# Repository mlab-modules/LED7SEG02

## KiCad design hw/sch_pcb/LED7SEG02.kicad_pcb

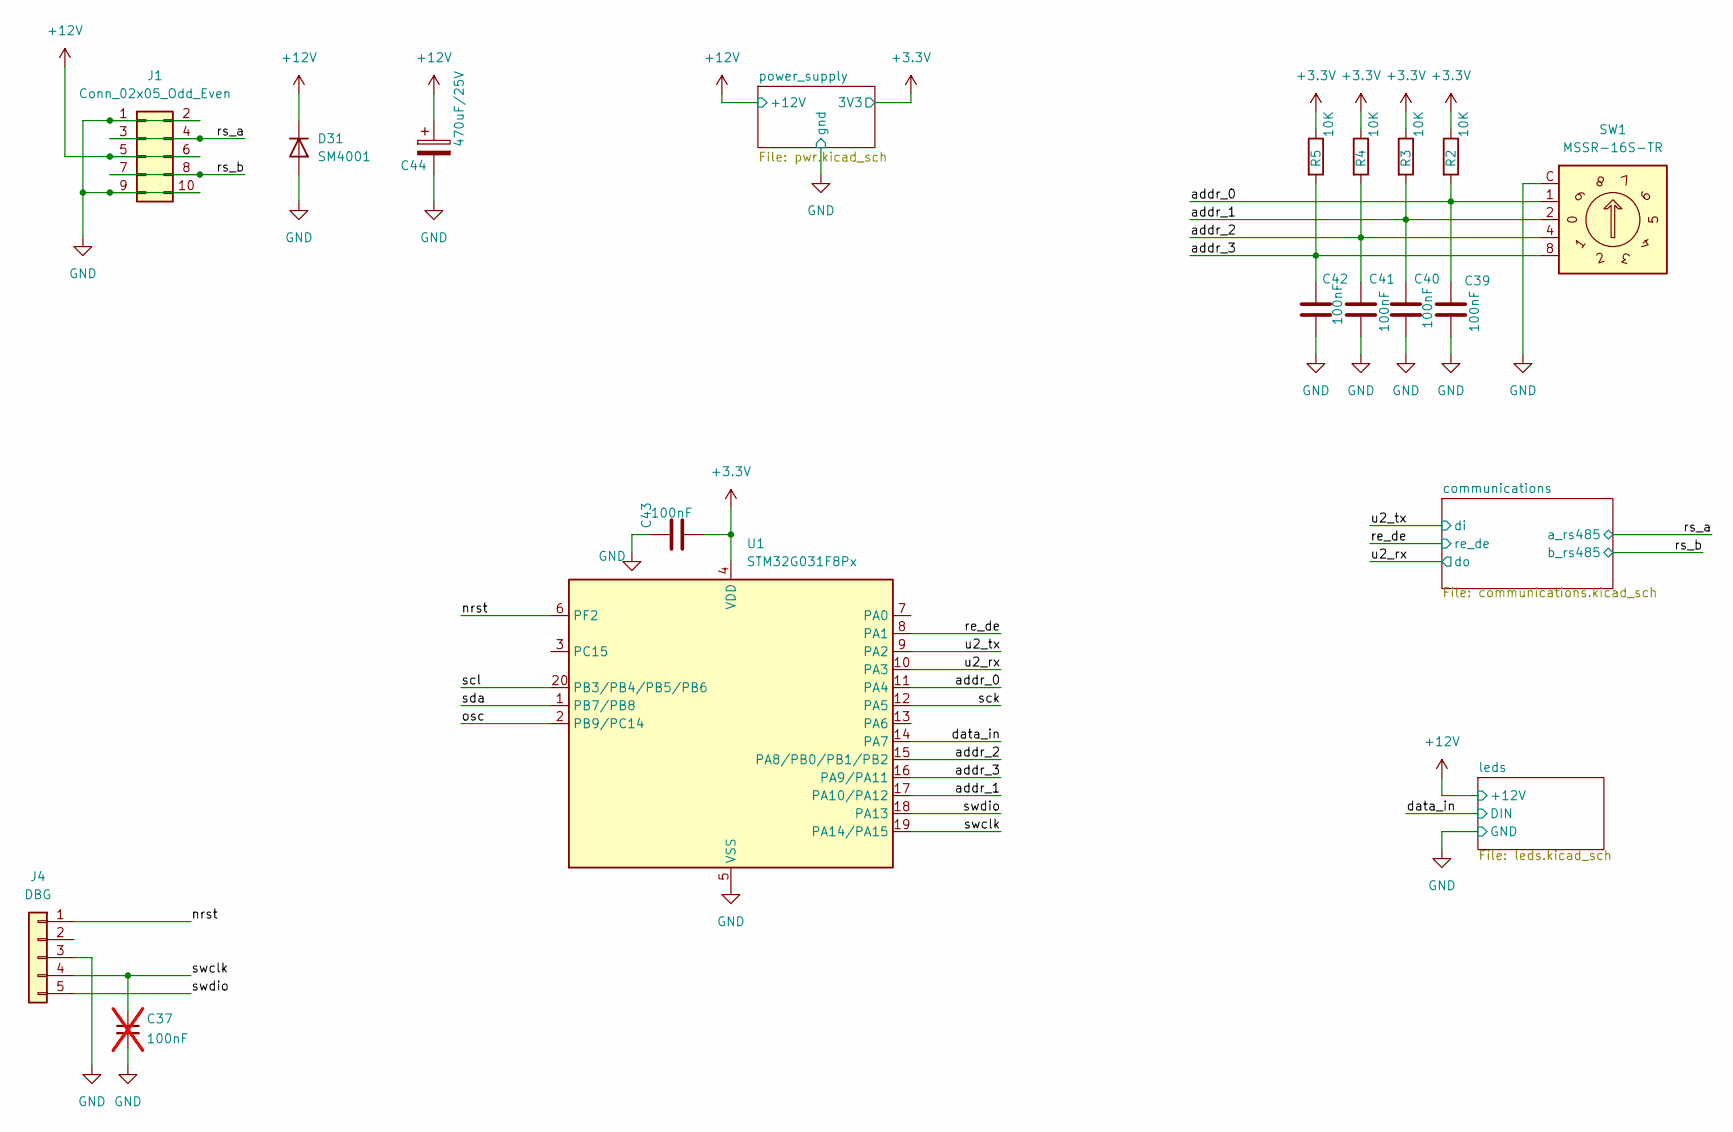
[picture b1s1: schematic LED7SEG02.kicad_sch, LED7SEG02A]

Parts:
C37: 100nF; C_0603_1608Metric_Pad1.08x0.95mm_HandSolder; not fitted
C39, C40, C41, C42, C43: 100nF; C_0603_1608Metric_Pad1.08x0.95mm_HandSolder
C44: 470uF/25V; CP_Elec_10x12.6
D31: SM4001; D_MELF
J1: Conn_02x05_Odd_Even; PinHeader_2x05_P2.54mm_Vertical
J4: DBG; Molex_PicoBlade_53047-0510_1x05_P1.25mm_Vertical
R2, R3, R4, R5: 10K; R_0603_1608Metric_Pad0.98x0.95mm_HandSolder
SW1: MSSR-16S-TR; Nidec_Copal_SH-7010B
U1: STM32G031F8Px; TSSOP-20_4.4x6.5mm_P0.65mm

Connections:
+3.3V: C43.2, R2.1, R3.1, R4.1, R5.1, U1.4 (VDD); also elsewhere on the board
+12V: C44.1, D31.1 (K), J1.5, J1.6; also elsewhere on the board
/addr_0: C39.1, R2.2, SW1.1, U1.11 (PA4)
/addr_1: C40.1, R3.2, SW1.2, U1.17 (PA10/PA12)
/addr_2: C41.1, R4.2, SW1.4, U1.15 (PA8/PB0/PB1/PB2)
/addr_3: C42.1, R5.2, SW1.8, U1.16 (PA9/PA11)
/data_in: U1.14 (PA7); also elsewhere on the board
/nrst: J4.1, U1.6 (PF2)
/osc: U1.2 (PB9/PC14)
/re_de: U1.8 (PA1); also elsewhere on the board
/rs_a: J1.3, J1.4; also elsewhere on the board
/rs_b: J1.7, J1.8; also elsewhere on the board
/sck: U1.12 (PA5)
/scl: U1.20 (PB3/PB4/PB5/PB6)
/sda: U1.1 (PB7/PB8)
/swclk: C37.1, J4.4, U1.19 (PA14/PA15)
/swdio: J4.5, U1.18 (PA13)
/u2_rx: U1.10 (PA3); also elsewhere on the board
/u2_tx: U1.9 (PA2); also elsewhere on the board
GND: C37.2, C39.2, C40.2, C41.2, C42.2, C43.1, C44.2, D31.2 (A), J1.1, J1.2, J1.9, J1.10, J4.3, SW1.C, U1.5 (VSS); also elsewhere on the board

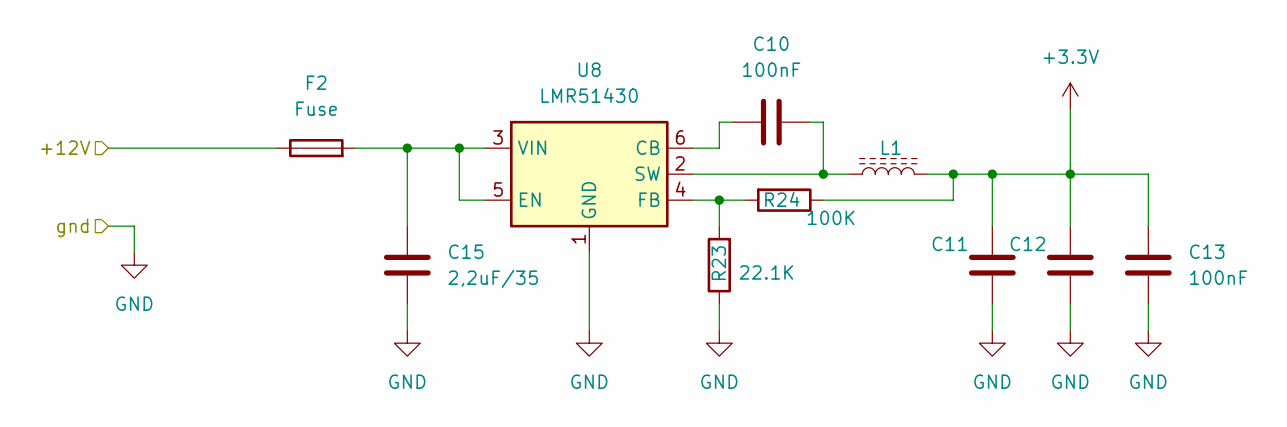
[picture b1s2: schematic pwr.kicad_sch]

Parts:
C10, C13: 100nF; C_0603_1608Metric_Pad1.08x0.95mm_HandSolder
C11, C12: CL10X106MO8NRNC; C_0603_1608Metric_Pad1.08x0.95mm_HandSolder
C15: 2,2uF/35; C_0603_1608Metric_Pad1.08x0.95mm_HandSolder
F2: Fuse; Fuse_1206_3216Metric_Pad1.42x1.75mm_HandSolder
L1: LQH5BPN4R7NT0L; L_APV_ANR5020
R23: 22.1K; R_0603_1608Metric_Pad0.98x0.95mm_HandSolder
R24: 100K; R_0603_1608Metric_Pad0.98x0.95mm_HandSolder
U8: LMR51430; SOT-23-6

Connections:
+3.3V: C11.2, C12.2, C13.1, L1.2, R24.1; also elsewhere on the board
+12V: F2.1; also elsewhere on the board
GND: C11.1, C12.1, C13.2, C15.2, R23.1, U8.1 (GND); also elsewhere on the board
unnamed: C10.1, U8.6 (CB)
unnamed: C15.1, F2.2, U8.3 (VIN), U8.5 (EN)
unnamed: R23.2, R24.2, U8.4 (FB)
unnamed: C10.2, L1.1, U8.2 (SW)

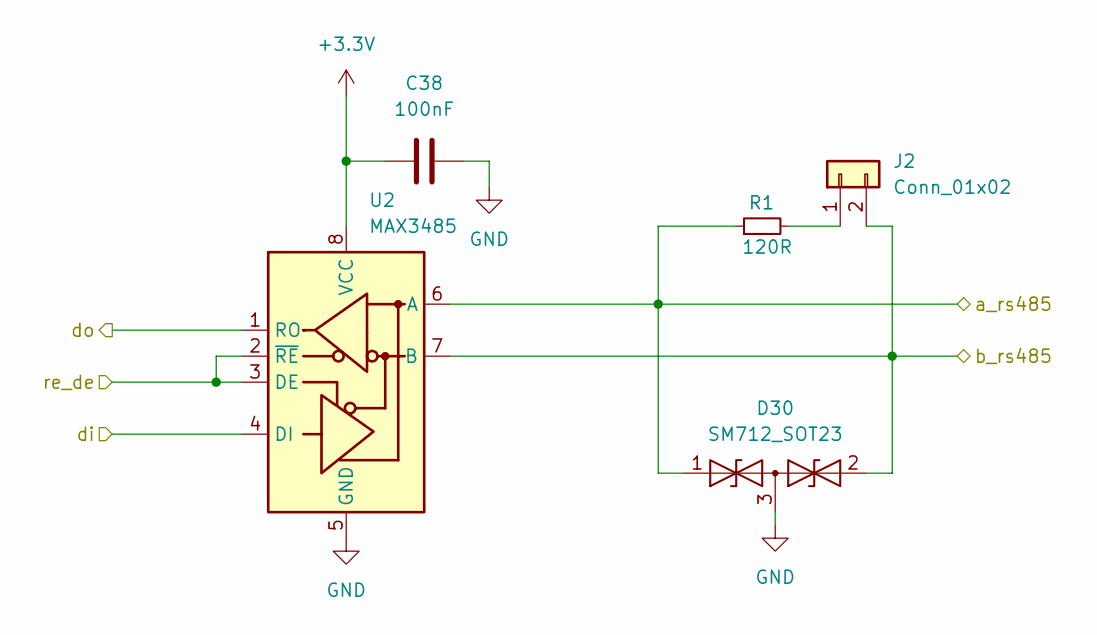
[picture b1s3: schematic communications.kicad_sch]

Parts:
C38: 100nF; C_0603_1608Metric_Pad1.08x0.95mm_HandSolder
D30: SM712_SOT23; SOT-23
J2: Conn_01x02; PinHeader_1x02_P2.54mm_Vertical
R1: 120R; R_0603_1608Metric_Pad0.98x0.95mm_HandSolder
U2: MAX3485; SOIC-8_3.9x4.9mm_P1.27mm

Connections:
+3.3V: C38.2, U2.8 (VCC); also elsewhere on the board
/re_de: U2.2 (~RE), U2.3 (DE); also elsewhere on the board
/rs_a: D30.1 (A1), R1.1, U2.6 (A); also elsewhere on the board
/rs_b: D30.2 (A2), J2.2, U2.7 (B); also elsewhere on the board
/u2_rx: U2.1 (RO); also elsewhere on the board
/u2_tx: U2.4 (DI); also elsewhere on the board
GND: C38.1, D30.3 (common), U2.5 (GND); also elsewhere on the board
unnamed: J2.1, R1.2

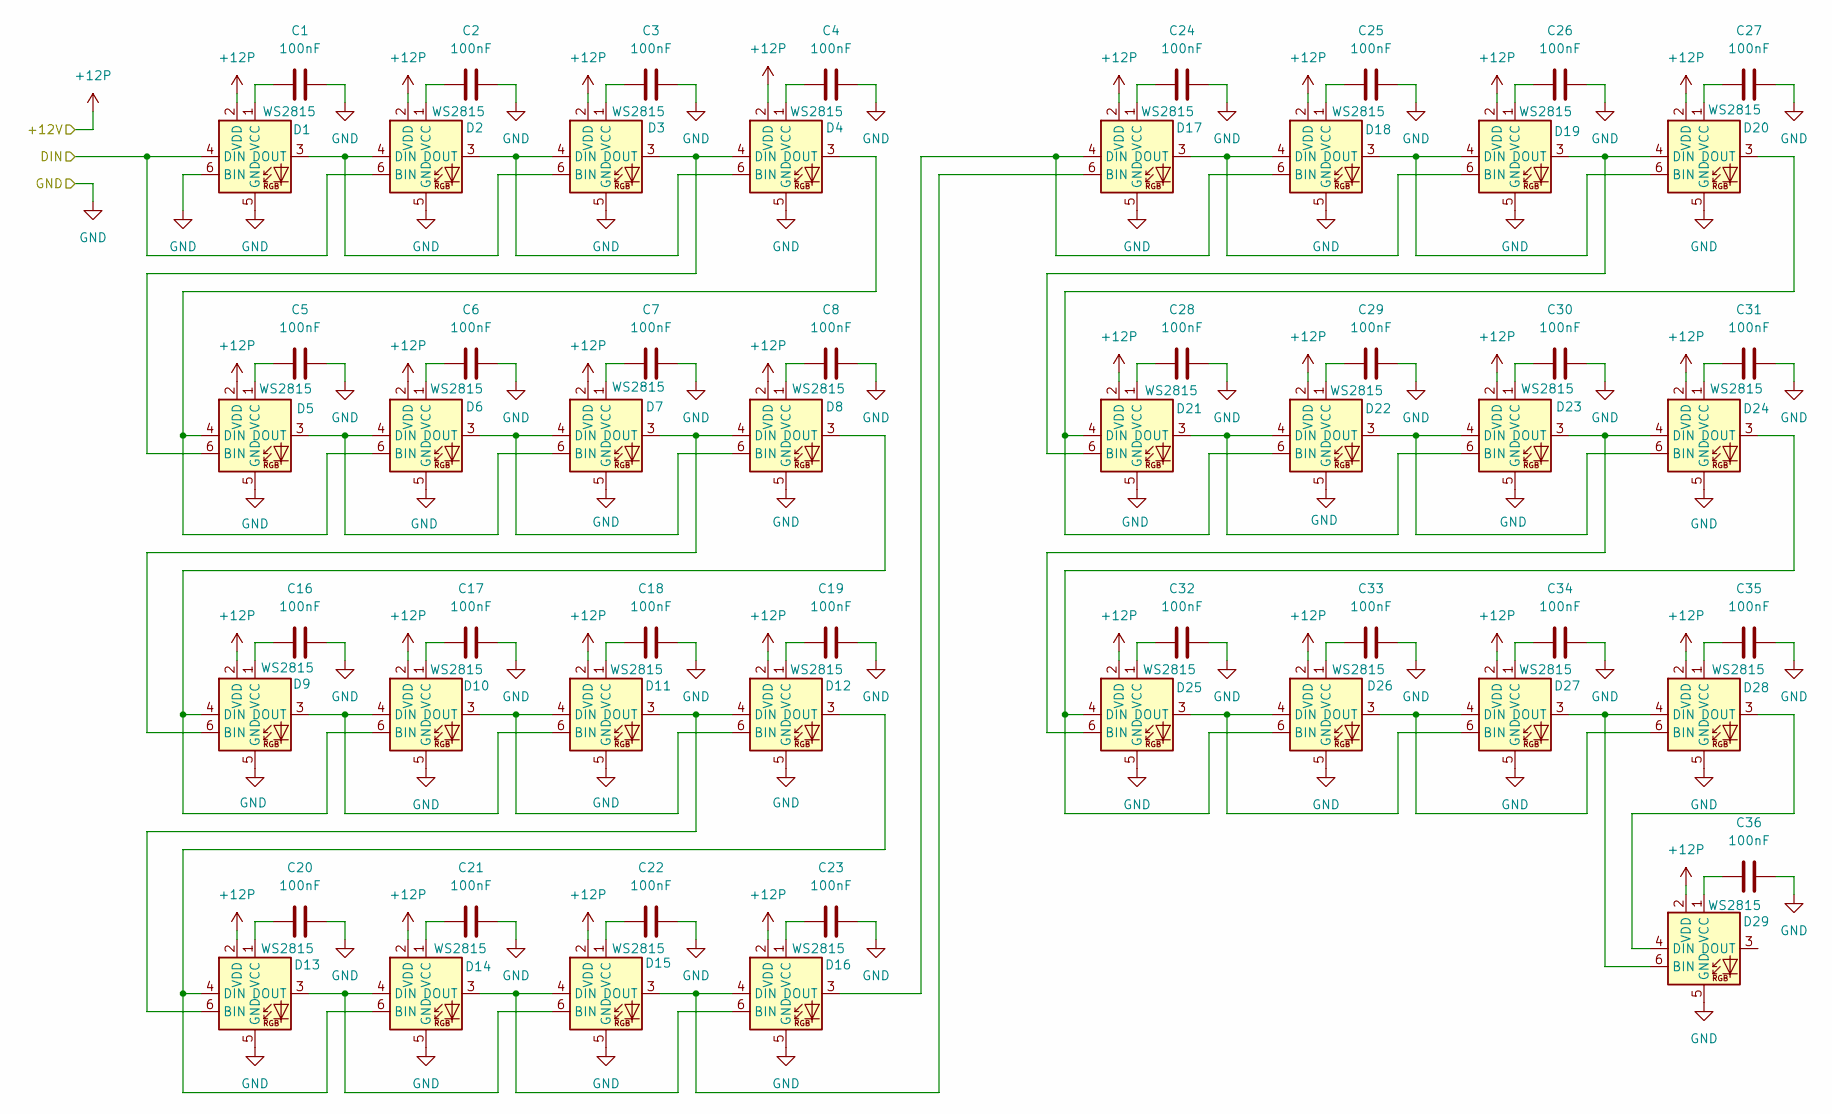
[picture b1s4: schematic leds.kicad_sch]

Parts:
C1, C2, C3, C4, C5, C6, C7, C8, C16, C17, C18, C19, C20, C21, C22, C23, C24, C25, C26, C27, C28, C29, C30, C31, C32, C33, C34, C35, C36: 100nF; C_0603_1608Metric_Pad1.08x0.95mm_HandSolder
D1, D2, D3, D4, D5, D6, D7, D8, D9, D10, D11, D12, D13, D14, D15, D16, D17, D18, D19, D20, D21, D22, D23, D24, D25, D26, D27, D28, D29: WS2815; LED_RGB_5050-6

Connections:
+12V: D1.2 (VDD), D2.2 (VDD), D3.2 (VDD), D4.2 (VDD), D5.2 (VDD), D6.2 (VDD), D7.2 (VDD), D8.2 (VDD), D9.2 (VDD), D10.2 (VDD), D11.2 (VDD), D12.2 (VDD), D13.2 (VDD), D14.2 (VDD), D15.2 (VDD), D16.2 (VDD), D17.2 (VDD), D18.2 (VDD), D19.2 (VDD), D20.2 (VDD), D21.2 (VDD), D22.2 (VDD), D23.2 (VDD), D24.2 (VDD), D25.2 (VDD), D26.2 (VDD), D27.2 (VDD), D28.2 (VDD), D29.2 (VDD); also elsewhere on the board
/data_in: D1.4 (DIN), D2.6 (BIN); also elsewhere on the board
GND: C1.1, C2.1, C3.1, C4.1, C5.1, C6.1, C7.1, C8.1, C16.1, C17.1, C18.1, C19.1, C20.1, C21.1, C22.1, C23.1, C24.1, C25.1, C26.1, C27.1, C28.1, C29.1, C30.1, C31.1, C32.1, C33.1, C34.1, C35.1, C36.1, D1.5 (GND), D1.6 (BIN), D2.5 (GND), D3.5 (GND), D4.5 (GND), D5.5 (GND), D6.5 (GND), D7.5 (GND), D8.5 (GND), D9.5 (GND), D10.5 (GND), D11.5 (GND), D12.5 (GND), D13.5 (GND), D14.5 (GND), D15.5 (GND), D16.5 (GND), D17.5 (GND), D18.5 (GND), D19.5 (GND), D20.5 (GND), D21.5 (GND), D22.5 (GND), D23.5 (GND), D24.5 (GND), D25.5 (GND), D26.5 (GND), D27.5 (GND), D28.5 (GND), D29.5 (GND); also elsewhere on the board
unnamed: D1.3 (DOUT), D2.4 (DIN), D3.6 (BIN)
unnamed: C1.2, D1.1 (VCC)
unnamed: D2.3 (DOUT), D3.4 (DIN), D4.6 (BIN)
unnamed: C2.2, D2.1 (VCC)
unnamed: D3.3 (DOUT), D4.4 (DIN), D5.6 (BIN)
unnamed: C3.2, D3.1 (VCC)
unnamed: D4.3 (DOUT), D5.4 (DIN), D6.6 (BIN)
unnamed: C4.2, D4.1 (VCC)
unnamed: D5.3 (DOUT), D6.4 (DIN), D7.6 (BIN)
unnamed: C5.2, D5.1 (VCC)
unnamed: D6.3 (DOUT), D7.4 (DIN), D8.6 (BIN)
unnamed: C6.2, D6.1 (VCC)
unnamed: D7.3 (DOUT), D8.4 (DIN), D9.6 (BIN)
unnamed: C7.2, D7.1 (VCC)
unnamed: C8.2, D8.1 (VCC)
unnamed: C16.2, D9.1 (VCC)
unnamed: D8.3 (DOUT), D9.4 (DIN), D10.6 (BIN)
unnamed: D9.3 (DOUT), D10.4 (DIN), D11.6 (BIN)
unnamed: D10.3 (DOUT), D11.4 (DIN), D12.6 (BIN)
unnamed: C17.2, D10.1 (VCC)
unnamed: D11.3 (DOUT), D12.4 (DIN), D13.6 (BIN)
unnamed: C18.2, D11.1 (VCC)
unnamed: D12.3 (DOUT), D13.4 (DIN), D14.6 (BIN)
unnamed: C19.2, D12.1 (VCC)
unnamed: D13.3 (DOUT), D14.4 (DIN), D15.6 (BIN)
unnamed: C20.2, D13.1 (VCC)
unnamed: D14.3 (DOUT), D15.4 (DIN), D16.6 (BIN)
unnamed: C21.2, D14.1 (VCC)
unnamed: D15.3 (DOUT), D16.4 (DIN), D17.6 (BIN)
unnamed: C22.2, D15.1 (VCC)
unnamed: D16.3 (DOUT), D17.4 (DIN), D18.6 (BIN)
unnamed: C23.2, D16.1 (VCC)
unnamed: D17.3 (DOUT), D18.4 (DIN), D19.6 (BIN)
unnamed: C24.2, D17.1 (VCC)
unnamed: D18.3 (DOUT), D19.4 (DIN), D20.6 (BIN)
unnamed: C25.2, D18.1 (VCC)
unnamed: D19.3 (DOUT), D20.4 (DIN), D21.6 (BIN)
unnamed: C26.2, D19.1 (VCC)
unnamed: D20.3 (DOUT), D21.4 (DIN), D22.6 (BIN)
unnamed: C27.2, D20.1 (VCC)
unnamed: D21.3 (DOUT), D22.4 (DIN), D23.6 (BIN)
unnamed: C28.2, D21.1 (VCC)
unnamed: D22.3 (DOUT), D23.4 (DIN), D24.6 (BIN)
unnamed: C29.2, D22.1 (VCC)
unnamed: D23.3 (DOUT), D24.4 (DIN), D25.6 (BIN)
unnamed: C30.2, D23.1 (VCC)
unnamed: D24.3 (DOUT), D25.4 (DIN), D26.6 (BIN)
unnamed: C31.2, D24.1 (VCC)
unnamed: D25.3 (DOUT), D26.4 (DIN), D27.6 (BIN)
unnamed: C32.2, D25.1 (VCC)
unnamed: D26.3 (DOUT), D27.4 (DIN), D28.6 (BIN)
unnamed: C33.2, D26.1 (VCC)
unnamed: D27.3 (DOUT), D28.4 (DIN), D29.6 (BIN)
unnamed: C34.2, D27.1 (VCC)
unnamed: D28.3 (DOUT), D29.4 (DIN)
unnamed: C35.2, D28.1 (VCC)
unnamed: C36.2, D29.1 (VCC)

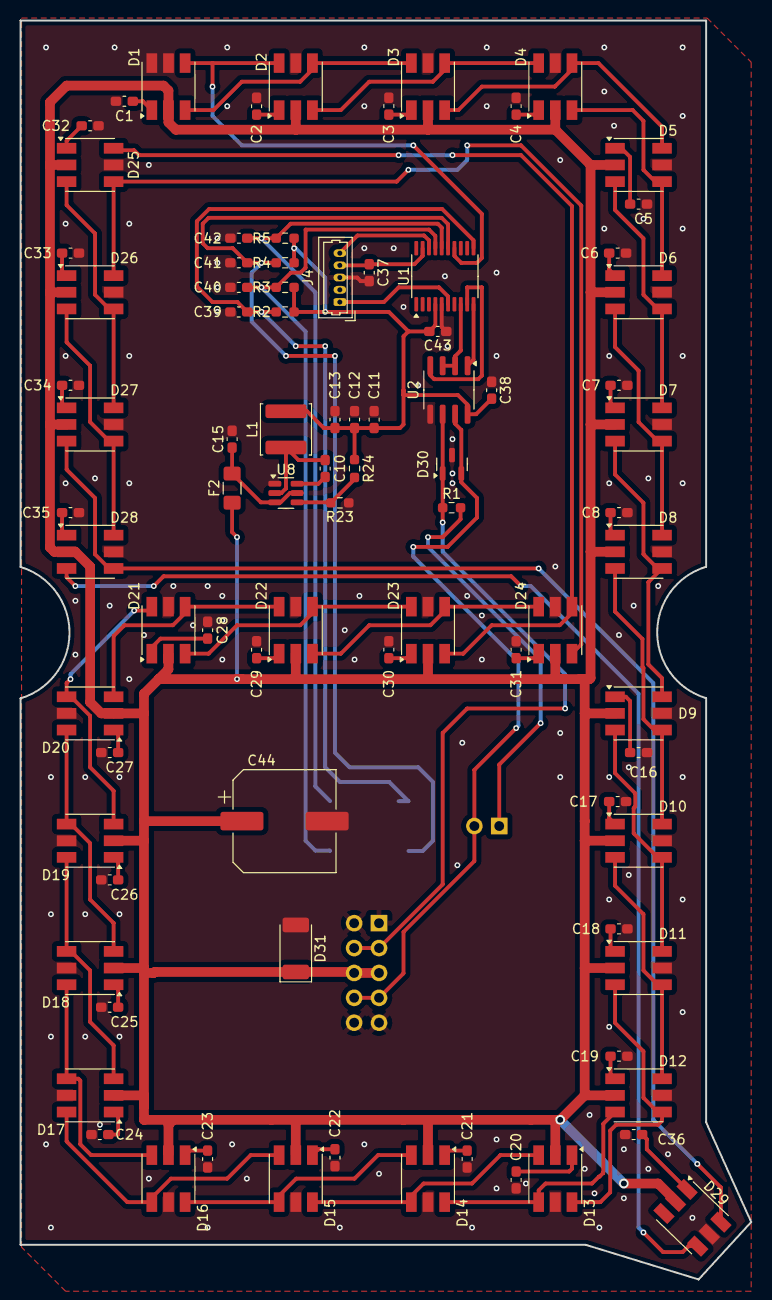
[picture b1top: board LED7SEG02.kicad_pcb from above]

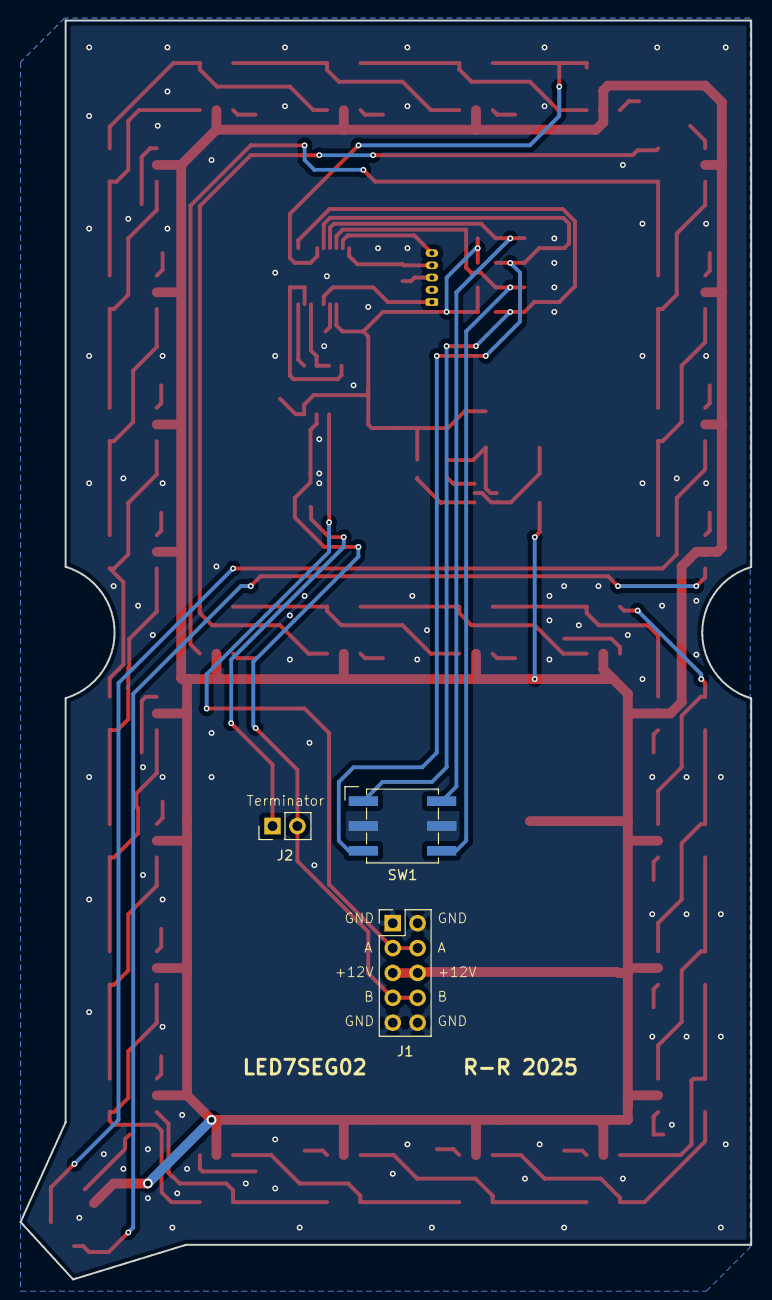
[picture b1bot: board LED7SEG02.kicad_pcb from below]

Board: 2 copper layers, 74.6 x 128.5 mm, 89 parts (3 on the bottom side), 78 nets.

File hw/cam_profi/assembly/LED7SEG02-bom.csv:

Component,Description,Part,References,Value,Footprint,Quantity Per PCB,Datasheet,sim.device,sim.pins
1,Unpolarized capacitor,C,C1C2C3C4C5C6C7C8C10C13C16C17C18C19C20C21C22C23C24C25C26C27C28C29C30C31C32C33C34C35C36C38C39C40C41C42C43,100nF,C_0603_1608Metric_Pad1.08x0.95mm_HandSolder,37,~,,
2,Unpolarized capacitor,C,C15,"2,2uF/35",C_0603_1608Metric_Pad1.08x0.95mm_HandSolder,1,~,,
3,Polarized capacitor,C_Polarized,C44,470uF/25V,CP_Elec_10x12.6,1,~,,
4,Unpolarized capacitor,C,C11C12,CL10X106MO8NRNC,C_0603_1608Metric_Pad1.08x0.95mm_HandSolder,2,~,,
5,"50V 1A General Purpose Rectifier Diode, MELF",SM4001,D31,SM4001,D_MELF,1,http://cdn-reichelt.de/documents/datenblatt/A400/SMD1N400%23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,D,1=K 2=A
6,"7V/12V, 600W Asymmetrical TVS Diode Array, SOT-23",SM712_SOT23,D30,SM712_SOT23,SOT-23,1,https://www.littelfuse.com/~/media/electronics/datasheets/tv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,,
7,,WS2815,D1D2D3D4D5D6D7D8D9D10D11D12D13D14D15D16D17D18D19D20D21D22D23D24D25D26D27D28D29,WS2815,LED_RGB_5050-6,29,https://www.tme.eu/Document/81275cf5ca3bcaa498439ec9fda98288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,,
8,Fuse,Fuse,F2,Fuse,Fuse_1206_3216Metric_Pad1.42x1.75mm_HandSolder,1,~,,
9,"Generic connector, single row, 01x02, script generated (kicad-library-utils/schlib/autogen/connector/)",Conn_01x02,J2,Conn_01x02,PinHeader_1x02_P2.54mm_Vertical,1,~,,
10,"Generic connector, double row, 02x05, odd/even pin numbering scheme (row 1 odd numbers, row 2 even numbers), script generated (kicad-library-utils/schlib/autogen/connector/)",Conn_02x05_Odd_Even,J1,Conn_02x05_Odd_Even,PinHeader_2x05_P2.54mm_Vertical,1,~,,
11,"Generic connector, single row, 01x05, script generated (kicad-library-utils/schlib/autogen/connector/)",Conn_01x05,J4,DBG,Molex_PicoBlade_53047-0510_1x05_P1.25mm_Vertical,1,~,,
12,Inductor with ferrite core,L_Ferrite,L1,LQH5BPN4R7NT0L,L_APV_ANR5020,1,~,,
13,"Resistor, small symbol",R_Small,R1,120R,R_0603_1608Metric_Pad0.98x0.95mm_HandSolder,1,~,,
14,Resistor,R,R2R3R4R5,10K,R_0603_1608Metric_Pad0.98x0.95mm_HandSolder,4,~,,
15,Resistor,R,R23,22.1K,R_0603_1608Metric_Pad0.98x0.95mm_HandSolder,1,~,,
16,Resistor,R,R24,100K,R_0603_1608Metric_Pad0.98x0.95mm_HandSolder,1,~,,
17,"Rotary switch, 4-bit encoding, 10 positions, Real code",SW_Coded_SH-7010,SW1,MSSR-16S-TR,Nidec_Copal_SH-7010B,1,https://www.nidec-copal-electronics.com/e/catalog/switch/sh-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,,
18,"4.5-V to 36-V, 3-A synchronous buck converter with 40-µA IQ, SOT-23-6",LMR51430,U8,LMR51430,SOT-23-6,1,https://www.ti.com/lit/ds/symlink/lmr51430.pdf,,
19,"True RS-485/RS-422, 10Mbps, Slew-Rate Limited, with low-power shutdown, with receiver/driver enable, 32 receiver drive capacitity, DIP-8 and SOIC-8",MAX3485,U2,MAX3485,SOIC-8_3.9x4.9mm_P1.27mm,1,https://datasheets.maximintegrated.com/en/ds/MAX3483-MAX3491.pdf,,
20,"STMicroelectronics Arm Cortex-M0+ MCU, 64KB flash, 8KB RAM, 64 MHz, 1.7-3.6V, 18 GPIO, TSSOP20",STM32G031F8Px,U1,STM32G031F8Px,TSSOP-20_4.4x6.5mm_P0.65mm,1,https://www.st.com/resource/en/datasheet/stm32g031f8.pdf,,

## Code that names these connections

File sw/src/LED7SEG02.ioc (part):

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Mcu.Name=STM32G031F(4-6-8)Px
Mcu.Package=TSSOP20
Mcu.UserName=STM32G031F8Px
PA1.Mode=Hardware Flow Control (RS485)
PA1.Signal=USART2_DE
PA11\ [PA9].GPIOParameters=GPIO_Label
PA11\ [PA9].GPIO_Label=addr_3
PA11\ [PA9].Signal=GPIO_Output
PA12\ [PA10].GPIOParameters=GPIO_Label
PA12\ [PA10].GPIO_Label=addr_1
PA12\ [PA10].Signal=GPIO_Output
PA13.Mode=Serial_Wire
PA13.Signal=SYS_SWDIO
PA14-BOOT0.Mode=Serial_Wire
PA14-BOOT0.Signal=SYS_SWCLK
PA14-BOOT0__PA15.StandardMode=true
PA2.Mode=Asynchronous
PA2.Signal=USART2_TX
PA3.Mode=Asynchronous
PA3.Signal=USART2_RX
PA4.GPIOParameters=GPIO_Label
PA4.GPIO_Label=addr_0
PA4.Signal=GPIO_Input
PA6.Signal=S_TIM3_CH1
PA7.GPIOParameters=GPIO_Label
PA7.GPIO_Label=WS2815
PA7.Signal=GPIO_Output
PB0.GPIOParameters=GPIO_Label
PB0.GPIO_Label=addr_2
PB0.Signal=GPIO_Output
PB0__PB1__PB2__PA8.StandardMode=true
PB3__PB4__PB5__PB6.StandardMode=true
PB6.Mode=I2C
PB6.Signal=I2C1_SCL
PB7.Mode=I2C
PB7.Signal=I2C1_SDA
PB7__PB8.StandardMode=true
PC14-OSC32_IN\ (PC14).Mode=HSE-External-Clock-Source
PC14-OSC32_IN\ (PC14).Signal=RCC_OSC_IN
PC14-OSC32_IN\ (PC14)__PB9.StandardMode=true
RCC.HSE_VALUE=8000000
RCC.SYSCLKFreq_VALUE=64000000
RCC.SYSCLKSource=RCC_SYSCLKSOURCE_PLLCLK
board=custom

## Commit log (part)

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2026-02-05 Update workflow files
2026-02-05 Update metadata files
2026-02-05 Intial commit
2026-02-07 Correct project documentation structure.
2026-02-07 Update actions products
2026-02-07 Correct project metadata.
